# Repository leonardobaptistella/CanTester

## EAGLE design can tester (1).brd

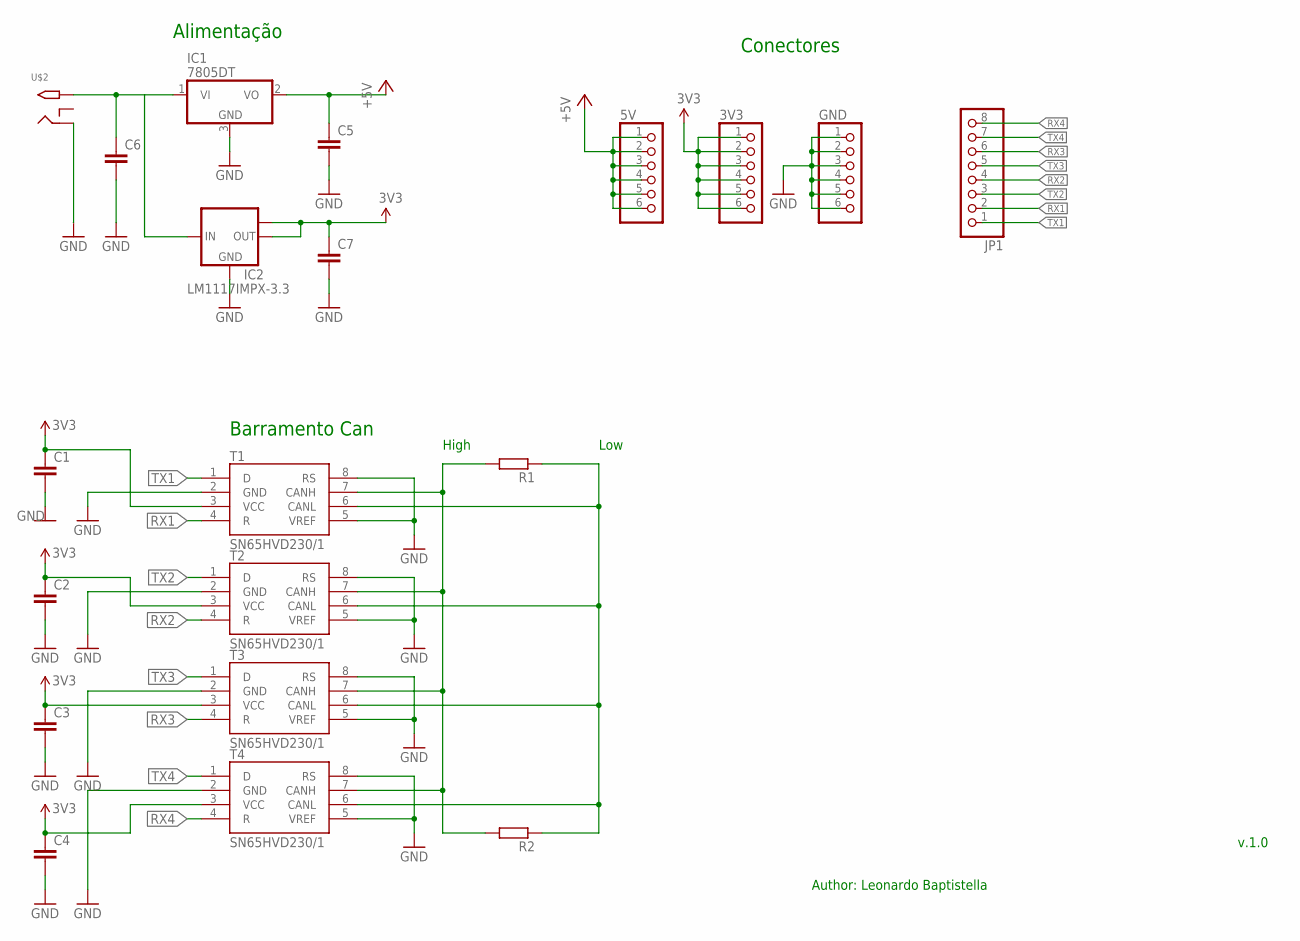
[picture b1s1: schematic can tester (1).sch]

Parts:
3V3, 5V: PINHD-1X6B; 1X06-BIG
C1, C2, C3, C4, C5, C6, C7: C-EUC1206K; C1206K
GND: PINHD-1X6B; 1X06-BIG
IC1: 7805DT; TO252
IC2: LM1117IMPX-3.3; SOT223
JP1: PINHD-1X8BIG; 1X08-BIG
R1, R2: R-EU_0204/7; 0204/7
T1, T2, T3, T4: SN65HVD230/1; SO8
U$2: 2.1MMJACKTHM; PJ-102A

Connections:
3V3: 3V3.1, 3V3.2, 3V3.3, 3V3.4, 3V3.5, 3V3.6, C1.1, C2.1, C3.1, C4.1, C7.1, IC2.2 (OUT), IC2.TAB (OUT1), T1.3 (VCC), T2.3 (VCC), T3.3 (VCC), T4.3 (VCC)
+5V: 5V.1, 5V.2, 5V.3, 5V.4, 5V.5, 5V.6, C5.1, IC1.2 (VO)
GND: C1.2, C2.2, C3.2, C4.2, C5.2, C6.2, C7.2, GND.1, GND.2, GND.3, GND.4, GND.5, GND.6, IC1.3 (GND), IC2.1 (GND), T1.2 (GND), T1.5 (VREF), T1.8 (RS), T2.2 (GND), T2.5 (VREF), T2.8 (RS), T3.2 (GND), T3.5 (VREF), T3.8 (RS), T4.2 (GND), T4.5 (VREF), T4.8 (RS), U$2.RING
unnamed: C6.1, IC1.1 (VI), IC2.3 (IN), U$2.TIP
unnamed: R1.1, R2.1, T1.6 (CANL), T2.6 (CANL), T3.6 (CANL), T4.6 (CANL)
unnamed: R1.2, R2.2, T1.7 (CANH), T2.7 (CANH), T3.7 (CANH), T4.7 (CANH)
RX1: JP1.2, T1.4 (R)
RX2: JP1.4, T2.4 (R)
RX3: JP1.6, T3.4 (R)
RX4: JP1.8, T4.4 (R)
TX1: JP1.1, T1.1 (D)
TX2: JP1.3, T2.1 (D)
TX3: JP1.5, T3.1 (D)
TX4: JP1.7, T4.1 (D)

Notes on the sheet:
Barramento Can
Alimentação
High
Low
Conectores
Author: Leonardo Baptistella
v.1.0

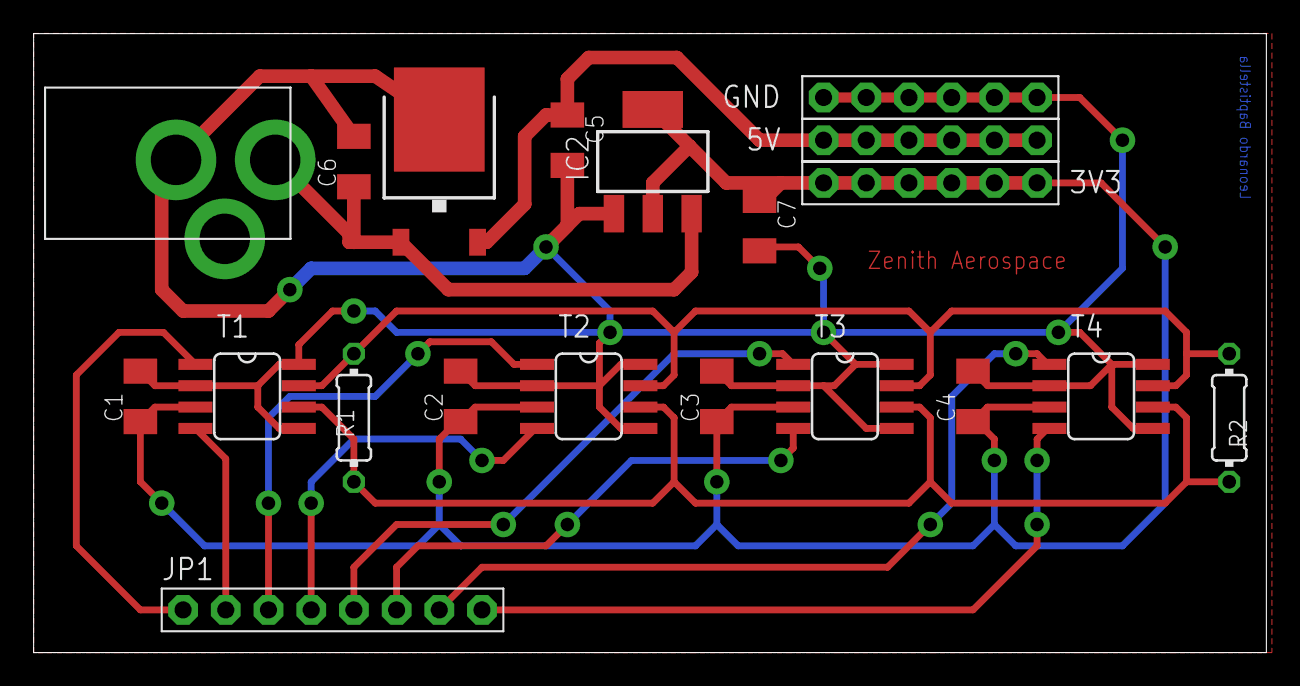
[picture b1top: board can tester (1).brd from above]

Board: 2 copper layers, 73.3 x 36.8 mm, 20 parts (0 on the bottom side), 14 nets.

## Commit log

2020-06-10 first

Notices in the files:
parts and their libraries:
SparkFun-Aesthetics: Licensing: Creative Commons ShareAlike 4.0 International - https://creativecommons.org/licenses/by-sa/4.0
FaBo-Supply: Released under the Creative Commons Attribution-ShareAlike 4.0 License
https://creativecommons.org/licenses/by-sa/4.0
